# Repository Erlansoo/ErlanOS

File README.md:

# ErlanOS

**An AI-native operating system, built from scratch.** The AI is the interface and the main
operator; the microkernel guarantees; an immutable core defines what can never be violated.
Every action the AI takes is structured, permission-checked and visible to the user, who can
review and change it.

- **Microkernel (x86-64, UEFI + Limine):** per-process paging, preemptive round-robin scheduler
  (PIT quantum, XSAVE context switch), Ring 3 processes, `int 0x80` syscalls, typed per-process
  capabilities and synchronous IPC. ACPI, LAPIC/IOAPIC, MSI/MSI-X, AHCI, NVMe and an own i8042 driver.
- **Erlan language:** own systems language with a bootstrap compiler (`erlan/erlancompiler.py`,
  Erlan to C). The kernel, the services, the network stack and the model runtime are written in it.
  Memory model: Rust's ownership, borrows and lifetimes, checked on a MIR-like IR (first slice landed).
- **Native LLM inference inside the OS:** the Ring 3 `model` service maps a GGUF file, tokenizes and
  runs CPU inference (Q8_0). Supports Llama, Qwen2 and Qwen3.5 (GatedDeltaNet + GQA attention).
- **AI Kernel API v0:** structured actions over IPC to an isolated `system` service (never shell
  commands), with message validation, permission tests and execution receipts.
- **Networking:** Intel e1000 driver and ARP/IPv4/UDP/TCP/DHCP/DNS written in Erlan; boots installed
  in a VirtualBox EFI VM with DHCP, DNS and HTTP working (`docs/VIRTUALBOX.md`).
- **Halo**, the companion workspace where you watch the AI work live:
  - Claude Code chats per project tab (official CLI, permission buttons, Remote Control), and an
    ELP1 gateway so the chat inside ErlanOS can reach an agent on the host.
  - KiCad without MCP: lossless S-expression engine, schematic builder, A* wiring, ERC/netlist
    oracle, `pcbnew` board engine, Freerouting and copper zones.
  - ngspice simulation, living Markdown + LaTeX documentation (MiKTeX, pandoc), a FreeCAD + BMesh
    3D space and JLCPCB fabrication outputs.

Architecture: [docs/ARQUITECTURA.md](docs/ARQUITECTURA.md). Status, build steps and details follow
in Spanish.

---

## Descripción (español)

Sistema operativo AI-native construido por capas. La IA es la interfaz, el operador
principal y, con el tiempo, el optimizador de partes de sí misma. El microkernel
garantiza; la IA decide; el Immutable Core define lo que nunca se viola.

Ver [docs/ARQUITECTURA.md](docs/ARQUITECTURA.md) para las capas, las decisiones
fijadas y el roadmap por rebanadas verticales.

## Estado

- M0: kernel arranca en QEMU (UEFI + Limine), framebuffer con `• • •`, log por serial.
- Erlan v0: `erlancompiler` (bootstrap en Python) compila los módulos `.e` del kernel.
  Pruebas en host: `make test`.
- M1: GDT, IDT con manejo de excepciones, PIC, timer PIT, teclado PS/2, memoria física
  (bitmap), heap del kernel y SSE/AVX habilitados.
- M2: paginación por proceso, TSS, scheduler round-robin con guardado XSAVE, procesos en
  Ring 3 cargados como módulos de Limine, syscalls por `int 0x80`, capabilities por
  proceso e IPC síncrono por endpoints. Primeros servicios de L2 (`init`, `echo`) en Erlan.
- M3: **una IA corre dentro de ErlanOS**. El servicio `model` (Ring 3, en Erlan) mapea un GGUF
  cargado por Limine, tokeniza y ejecuta inferencia en la consola gráfica. El runtime
  Erlan admite Llama, Qwen2 y Qwen3.5 de texto (GatedDeltaNet + atención GQA).
  Modelo principal: Qwen3.5-2B Q8_0; perfil de código: Qwen2.5-Coder-1.5B-Instruct Q8_0.
- M4: AI Kernel API v0 por IPC hacia el servicio aislado `system`: consulta de estado,
  modo visual normal/foco y panel de estado del kernel. Recibos de ejecución, validación
  de mensajes y pruebas de permisos. Los comandos directos funcionan con todos los
  modelos; el clasificador experimental `/ai` sólo está validado con SmolLM2 y se
  abstiene con Qwen hasta validar su selección de acciones.
  Detalles, formato y límites en [docs/M4.md](docs/M4.md).
- N0: **ErlanOS llega a internet**. Driver Intel e1000 en L1 (`kernel/src/e1000.e`) y pila
  ARP/IPv4/UDP/DHCP/DNS en Erlan (`net/`). En QEMU con red de usuario obtiene dirección por
  DHCP y resuelve un nombre público a través del resolver real del host. Verificado por
  serial, captura pcap y el resolver del host: `make test-net`. Detalles en [docs/RED.md](docs/RED.md).

## Construir y ejecutar

Editor experimental **Documentos D0**: hoja sobre el lienzo café, redacción con
Qwen, edición con teclado y control nativo de papel, fuentes y márgenes espejo.
En PowerShell: `.\scripts\run_document_editor.ps1`. Dentro del SO: `crea un documento`
o `Redacta un informe breve sobre energia solar`. La edición vive en ErlanOS;
PDF/DOCX/ODT se convierten mediante un puente temporal en el anfitrión y el estado
del guest sigue en RAM. Alcance y comandos en [docs/DOCUMENTOS.md](docs/DOCUMENTOS.md).

El soporte actual está validado en QEMU y, desde el 26/10/2026, también en una VM de
**VirtualBox** con firmware EFI en esta PC: arranque, consola, teclado PS/2, modelo cargado y la
pila de red completa (DHCP, DNS, TCP, HTTP) sobre el 82540EM emulado. Script y evidencia:
`scriptsbox_erlanos.ps1` y [docs/VIRTUALBOX.md](docs/VIRTUALBOX.md). GPU de cómputo e
instalación física siguen pendientes; evaluación del equipo y propuesta en
[docs/HARDWARE-REAL.md](docs/HARDWARE-REAL.md).

Windows (Git Bash):

```bash
bash scripts/setup-windows.sh   # una vez: LLVM, QEMU, make (winget) + Limine
source scripts/env.sh           # en cada shell nueva
make run                        # Qwen3.5-2B, disco GPT/FAT32 real, 4 GiB de RAM
# Cierra la VM anterior antes de cambiar de perfil:
make run MODEL=coder            # Qwen2.5-Coder-1.5B-Instruct
```

`make run` detecta WHPX en Windows o KVM en Linux/WSL y comprueba que QEMU puede
inicializarlo. Si no está disponible, informa la causa y usa TCG. Para WHPX hacen
falta virtualización en firmware y la característica Windows Hypervisor Platform;
el detector no cambia opciones del sistema. Comprueba la selección con
`python scripts/qemu_accel.py`. Para forzar emulación durante depuración:
`make run QEMU_ACCEL='-accel tcg -cpu max'`.

Los modelos seleccionados deben existir en `models/`; quedan fuera de git. La imagen
contiene un solo GGUF. Descargas verificadas, perfiles y límites en
[docs/QWEN.md](docs/QWEN.md). `make run MODEL=smollm` conserva el perfil histórico.
También se puede indicar un archivo compatible con `MODEL_FILE=models/archivo.gguf`.

Prueba del mismo runtime fuera de QEMU:
`bash scripts/test_chat_host.sh --model models/qwen3.5-2b-q8_0.gguf --semantic`.

Dentro de QEMU: `/estado`, `/modo foco`, `/modo normal`, `/panel`, `/ayuda`.
Para selección experimental con SmolLM2: `/ai Read system status`,
`/ai Enable focus mode`, `/ai Switch to normal mode`, `/ai Show status panel`.
El texto sin `/` sigue funcionando como chat. `/ai` reinicia el contexto de chat.
El chat usa un mensaje de sistema breve, sin ejemplos de respuestas, con
un máximo de 64 tokens por turno. `Enter` envía; `Shift+Enter` inserta una nueva
línea para escribir código (hasta 240 bytes por petición).
`Esc` detiene el chat o la interpretación `/ai`;
las otras teclas escritas durante la espera se conservan. La consola admite
acentos y ñ en UTF-8. Los modelos pequeños pueden equivocarse; pruebas actuales en
[docs/QWEN.md](docs/QWEN.md) e historial de SmolLM2 en [docs/CHAT-NATIVO.md](docs/CHAT-NATIVO.md).

TCG emula la CPU: los primeros tokens aún pueden tardar. El halo indica trabajo;
no hay una pausa artificial entre letras. `/estado` y `/panel` dan una respuesta
directa sin ejecutar inferencia.

Pruebas: `make test-m4-host` y `make test-m4`. Para incluir selección real del modelo:
`python scripts/qemu_m4_test.py --ai --model models/smollm2-135m-instruct-q8_0.gguf --timeout 1200 --command-timeout 600`.
Cada prueba usa una VM e imagen privadas y guarda recibos, resultado y captura en `build/`.
Regresión del chat: `bash scripts/test_chat_host.sh --model models/qwen3.5-2b-q8_0.gguf --semantic` y
`python scripts/qemu_chat_test.py --semantic --model models/qwen3.5-2b-q8_0.gguf --accel whpx --timeout 1500`.
Para probar con aceleración de Windows, añade `--accel whpx`.
Benchmark numérico: `python scripts/test_matmul_host.py --model models/smollm2-135m-instruct-q8_0.gguf`.

WSL2 Ubuntu (requiere virtualización activa en BIOS; da KVM):

```bash
bash scripts/setup-wsl.sh
make run
```

Todo el código fuente del sistema está en Erlan: desde el 26/10/2026 `kernel/`, `services/`,
`net/` y `mind/` no tienen ningún archivo C propio (instrucciones privilegiadas, Limine,
`kprintf`, los stubs de interrupción, el `_start` de los servicios y la plataforma del modelo
son módulos `.e`); quedan los datos generados de las fuentes, el runtime del compilador y los
arneses de prueba. Qué se añadió al lenguaje y qué falta: [docs/ERLAN-SISTEMA.md](docs/ERLAN-SISTEMA.md).
El mismo día entraron el driver **AHCI** (`kernel/src/ahci.e`: el espacio persistente D1 monta
también desde un disco SATA, en QEMU y en VirtualBox, [docs/WORKSPACE.md](docs/WORKSPACE.md)) y
**ACPI + APIC + MSI** (`acpi.e`, `apic.e`, `pci_msi.e`: tablas ACPI leídas, el reloj del sistema en
el temporizador del LAPIC y las completaciones del AHCI por MSI, [docs/APIC.md](docs/APIC.md)).

## Layout

```
kernel/    L1  microkernel en Erlan (memoria, interrupciones, scheduler, IPC, capabilities); kernel/entry: kmain de las imágenes de prueba
services/  L2  servicios de usuario en Erlan (init, echo, system, model runtime)
mind/      L3  controlador de acciones M4; router y memoria después
caps/      L4  capabilities de dominio (Electronics/KiCad, MCU target packs, CAD)
erlan/     lenguaje Erlan: erlancompiler (bootstrap), runtime mínimo, pruebas
docs/      arquitectura, decisiones, specs
scripts/   setup y utilidades
```

### Espacio 3D de Halo

FreeCAD y BMesh mediante APIs nativas, en un lienzo común independiente de la PCB: [uso, contrato y límites](docs/HALO-ESPACIO-3D.md). Incluye proyectos persistentes, parámetros, historial y exportación nativa/STEP/STL. Abrir `http://127.0.0.1:8765/?pestana=espacio3d` con `python -m halo.servidor` (un solo servidor, puerto 8765).

### La IA dentro del Halo

Cada pestaña tiene sus chats de Claude Code (etapa 3 del plan): sesiones oficiales del binario sin modificar, permisos por botones, consola y Remote Control. Las conversaciones de agentes de la etapa de Codex se retiraron el 20/09/2026.

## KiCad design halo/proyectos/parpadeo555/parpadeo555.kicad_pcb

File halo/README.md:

# Halo

Programa propio donde se ve, en vivo y sobre el fondo café, el trabajo que hace la IA.
Esquemáticos y placas de KiCad construidos con control nativo, sin MCP.

Incluye revisiones de proyecto, bloqueo entre procesos, verificación sin falsos
positivos, símbolos multipartes y consultas `/api/contexto` y `/api/capacidades`.
La página y el servidor deben recargarse después de actualizar el código.

```
Halo.exe                                    # arranca el servidor si hace falta y abre la ventana del Halo
python -m halo.servidor                     # sólo el servidor local en 127.0.0.1:8765
powershell -File halo\lanzador\construir.ps1  # vuelve a compilar Halo.exe y su icono (C# de Windows)
python halo\proyectos\parpadeo555\disenar.py   # la IA diseña; el Halo lo muestra paso a paso
python halo\pruebas\test_nativo.py          # el motor contra KiCad
python halo\pruebas\test_vista_pcb.py       # la vista de placas sobre las demos de KiCad
```

Placa por etapas, con el Python de KiCad:

```
"%LOCALAPPDATA%\Programs\KiCad\10.0\bin\python.exe" -m halo.kicad.pcb halo\proyectos\parpadeo555 crear
... acomodar | rutear [--motor freerouting] [--redes A,B] | zona GND B.Cu | verificar
```

| Carpeta | Qué hace |
|---|---|
| `servidor.py` | sirve la interfaz y empuja cambios por Server-Sent Events; sin sondeo en reposo |
| `vigia.py` | avisos de cambio de archivos del sistema (ReadDirectoryChangesW), sin dependencias |
| `proyectos.py` | proyectos como pestañas: estado inicial de una carpeta, nombre, aviso de apertura de los motores |
| `lanzador/` | `Halo.exe`: Halo.cs, el icono dibujado en Python y el script que los compila; `capturar.py` fotografía una página del Halo con Edge sin ventana por DevTools (evidencias) |
| `chat/servicio.py` | chats de Claude Code por proyecto: un proceso del binario oficial por turno (flujo JSON), permisos, detener, ramas, consola y Remote Control |
| `chat/transcripcion.py` | historial leído de la transcripción oficial de Claude Code (`~/.claude/projects`) |
| `documentos/servicio.py` | documentación viva en `<carpeta>/docs`: memoria Markdown e informe LaTeX con secciones generadas que avisan cuando su fuente cambió; figuras con kicad-cli, PDF con MiKTeX, pandoc; guía de etapas |
| `documentos/datos.py`, `plantillas.py`, `markdown.py`, `cli.py` | lo que el proyecto sabe de sí mismo, las plantillas, el conversor Markdown→HTML sin dependencias y la orden `python -m halo.documentos.cli` |
| `editor.py` | tus cambios a mano en esquemático y placa, con copia previa y deshacer |
| `ui/` | ventana: halo, lienzos 2D con zoom y arrastre, capas, panel de verificación, bitácora, chat, documentos; una sola base de botones en `halo.css` |
| `jev.py` | segunda opinión de Jev (TypeSafe): decisión tipada con probabilidad y confianza; clave sólo en `TYPESAFE_API_KEY` |
| `kicad/sexpr.py` | lee y escribe el formato S-expresión de KiCad sin pérdida |
| `kicad/biblioteca.py` | símbolos oficiales instalados, aplanando los derivados |
| `kicad/geometria.py` | la misma matriz de rotación y espejo que usa eeschema |
| `kicad/esquematico.py` | constructor: colocar, cablear, potencia, etiquetas, bloques, mover módulos, deshacer, guardar |
| `kicad/ruteo.py` | enrutado ortogonal A* que no toca cuerpos, pines ni cables ajenos |
| `kicad/reglas.py` | revisión de dibujo: solapes, cables sobre cuerpos, extremos sueltos, cruces |
| `kicad/oraculo.py` | KiCad juzga: ERC, netlist comparada con la intención, SVG |
| `kicad/sesion.py` | estado del halo y bitácora con recibos, visibles al instante |
| `kicad/vista.py` | convierte cualquier `.kicad_sch` en dibujo para el lienzo |
| `kicad/placa.py` | motor de placa con `pcbnew`: crear, colocar en dos caras, rutear, reglas, serigrafía, verificar |
| `kicad/acomodo.py` | acomodo con oficio: módulos, calor, altura, señales rápidas, dos caras, rótulos |
| `kicad/perfil.py` | perfil de cada huella: altura del modelo 3D, calor, sensibilidad, señales rápidas |
| `kicad/cobre.py` | cobre por zonas: prioridades, planos divididos, áreas prohibidas, costura, bajadas a plano |
| `kicad/clases.py` | clases de red del `.kicad_pro`: ancho, holgura y vía por red |
| `kicad/pcb.py` | las etapas de la placa desde la línea de comandos |
| `kicad/freerouting.py` | Freerouting supervisado: DSN con las reglas por red, sin interfaz |
| `kicad/vista_pcb.py` | convierte un `.kicad_pcb` (2 a 8 capas) en dibujo: zonas, capas con nombre, dos caras, pendientes |

Pruebas con el Python de KiCad: `halo\pruebas\test_placa.py` (cobre, dos caras, perfil, serigrafía).

Plan de trabajo por etapas: `docs/HALO-PLAN.md`.

### Icono

La **aureola**: un anillo dorado que flota sobre los tres puntos crema del Halo, en un cuadro café de
esquinas redondeadas. `lanzador/icono.py` lo dibuja con campos de distancia con signo (cuadro redondeado,
elipse, círculos) y supermuestreo por pixel (4×4 hasta 64 px, 3×3 en 128 y 256), sin bibliotecas gráficas.

| Salida | Contenido | Quién la usa |
|---|---|---|
| `build/halo/halo.ico` | 16, 24, 32, 48, 64, 128 y 256 px, una imagen PNG por tamaño | `construir.ps1` la incrusta en `Halo.exe` (`/win32icon`) |
| `halo/ui/halo.png` | 64 px | favicon de la página: Edge lo usa como icono de la ventana y de la barra de tareas |

- Cada tamaño se dibuja aparte; en 24 px o menos la aureola y los puntos engordan y se quitan los brillos para que se lean.
- `construir.ps1` vuelve a dibujar el icono antes de compilar `Halo.exe`.
- `ui/index.html` pide el favicon como `/halo.png?v=aureola`. Edge guarda los favicons por dirección en el perfil de la ventana
  (`build/halo/ventana`), así que **al cambiar el icono hay que cambiar ese `?v=`**; el servidor ignora la consulta.
- Un acceso directo de Windows debe tomar el icono de `Halo.exe,0`: si apunta a `build/halo/halo.ico`, el explorador sigue
  mostrando el de su caché aunque el archivo cambie. `ie4uinit.exe -show` refresca esa caché.

### Simulación eléctrica

La pestaña **Simulación** integra ngspice: punto de operación, transitorio y AC,
curvas, mediciones, historial y cancelación. Incluye ejemplos RC y 555 ideal.
Para agentes: `python -m halo.simulacion --ejemplo rc` o `/api/simulacion`.
Configuración de modelos, API, pruebas y límites: [HALO-SIMULACION.md](../docs/HALO-SIMULACION.md).

### Fabricación

El panel PCB/3D incluye **Preparar para JLCPCB**: DRC, Gerbers, taladros e informe
ligado a la revisión. Exportar no aprueba el diseño ni realiza un pedido.
API para agentes: `/api/fabricacion`.

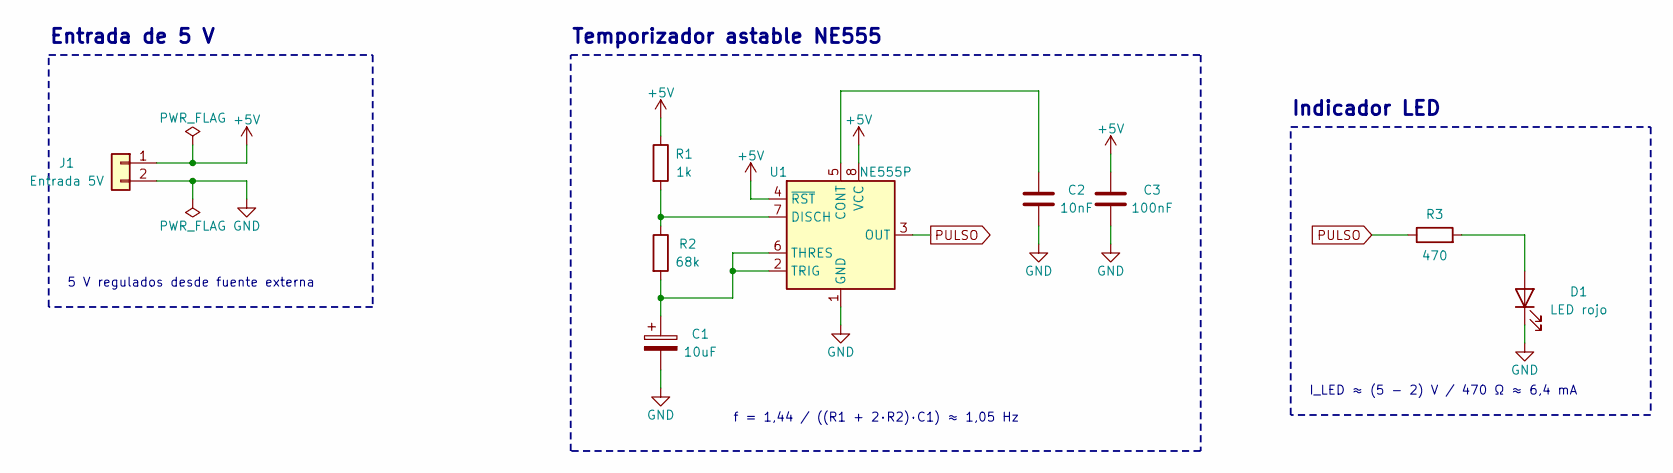
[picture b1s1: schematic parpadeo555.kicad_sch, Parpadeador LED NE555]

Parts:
C1: 10uF; CP_Radial_D5.0mm_P2.00mm
C2: 10nF; C_Disc_D5.0mm_W2.5mm_P5.00mm
C3: 100nF; C_Disc_D5.0mm_W2.5mm_P5.00mm
D1: LED rojo; LED_D5.0mm
J1: Entrada 5V; PinHeader_1x02_P2.54mm_Vertical
R1: 1k; R_Axial_DIN0207_L6.3mm_D2.5mm_P10.16mm_Horizontal
R2: 68k; R_Axial_DIN0207_L6.3mm_D2.5mm_P10.16mm_Horizontal
R3: 470; R_Axial_DIN0207_L6.3mm_D2.5mm_P10.16mm_Horizontal
U1: NE555P; DIP-8_W7.62mm

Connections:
+5V: C3.1, J1.1, R1.1, U1.4 (~RST), U1.8 (VCC)
GND: C1.2, C2.2, C3.2, D1.1 (K), J1.2, U1.1 (GND)
unnamed: D1.2 (A), R3.2
unnamed: C2.1, U1.5 (CONT)
unnamed: R1.2, R2.1, U1.7 (DISCH)
unnamed: C1.1, R2.2, U1.2 (TRIG), U1.6 (THRES)
PULSO: R3.1, U1.3 (OUT)

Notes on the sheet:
Entrada de 5 V
Temporizador astable NE555
Indicador LED
5 V regulados desde fuente externa
f = 1,44 / ((R1 + 2·R2)·C1) ≈ 1,05 Hz
I_LED ≈ (5 − 2) V / 470 Ω ≈ 6,4 mA

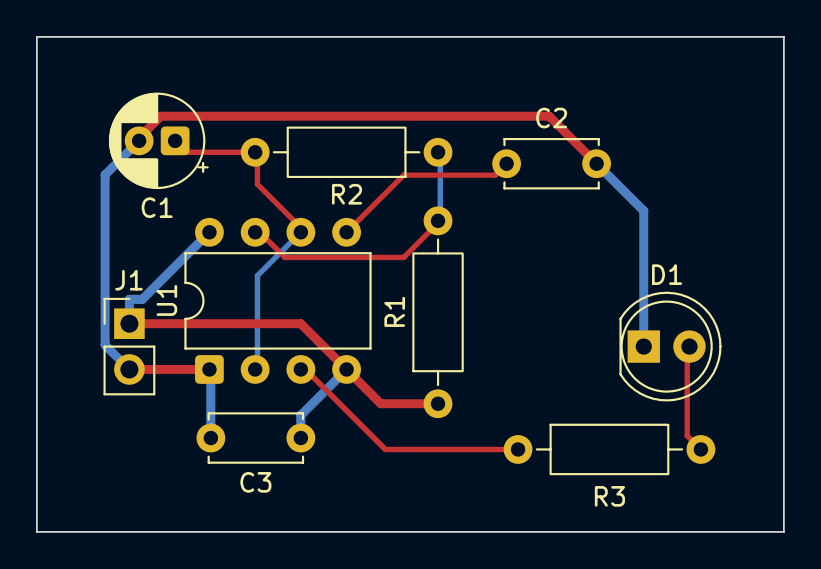
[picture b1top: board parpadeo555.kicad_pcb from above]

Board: 2 copper layers, 41.5 x 27.5 mm, 9 parts (0 on the bottom side), 7 nets.
